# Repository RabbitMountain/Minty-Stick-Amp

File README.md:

# Minty-Stick-Amp
DIY headphone Amplifier for the Chapman Stick

Design in Autodesk Eagle CAD, by me, Andrew Barney, December 2021. **Prototype not yet tested.**

This design is a heavily modified derivitave based on the **"Stick Amp"** by Marcelo Privé, designed and shared sometime between 2002 and 2004. Marcelo Privé's amp was an improved version of Chris Crain's original Chapman **"Stick® Player’s Headphone Amplifier"**, which was built and shared online sometime before 2003. Both designs were centered around the 1969 LM386 Low Voltage Audio Power Amplifier.

The LM386 is one of the most common amps used in DIY guitar preamplifiers due to its ability to run on a single 9V battery. The well-known "Smokey Amp" uses an LM386 and is notable for being able to fit in a cigarette package. The "Ruby" amp is a modified version of a Little Gem amplifier.

In contrast, this prototype design is designed around the more modern LM4819 and TPA321. The design should be compatible with any of the following chips that have the same basic pinout for the SOIC package. Possible IC chips include: LM4819, LM4818?, TPA751, TPA321, TPA741, TPA721, TPA711?, TPA701, TPA301. By using a more modern chip like the LM4819 or the TPA*** family means that it can run on between 2.5 VDC – 5.5 VDC. This means we can run it on a 3.7/4.2V Lipo battery instead of a large 9V battery. Low Power and small size were the main goals of this design, as well as (hopefully) being a functional christmas present for my brother Simmon.

# Schematic

# Sources:

https://web.archive.org/web/20041211021643/http://home.earthlink.net/~cscrain/stick/shpamp.html

https://www.stickist.com/gallery/viewpic.php?pic_id=317

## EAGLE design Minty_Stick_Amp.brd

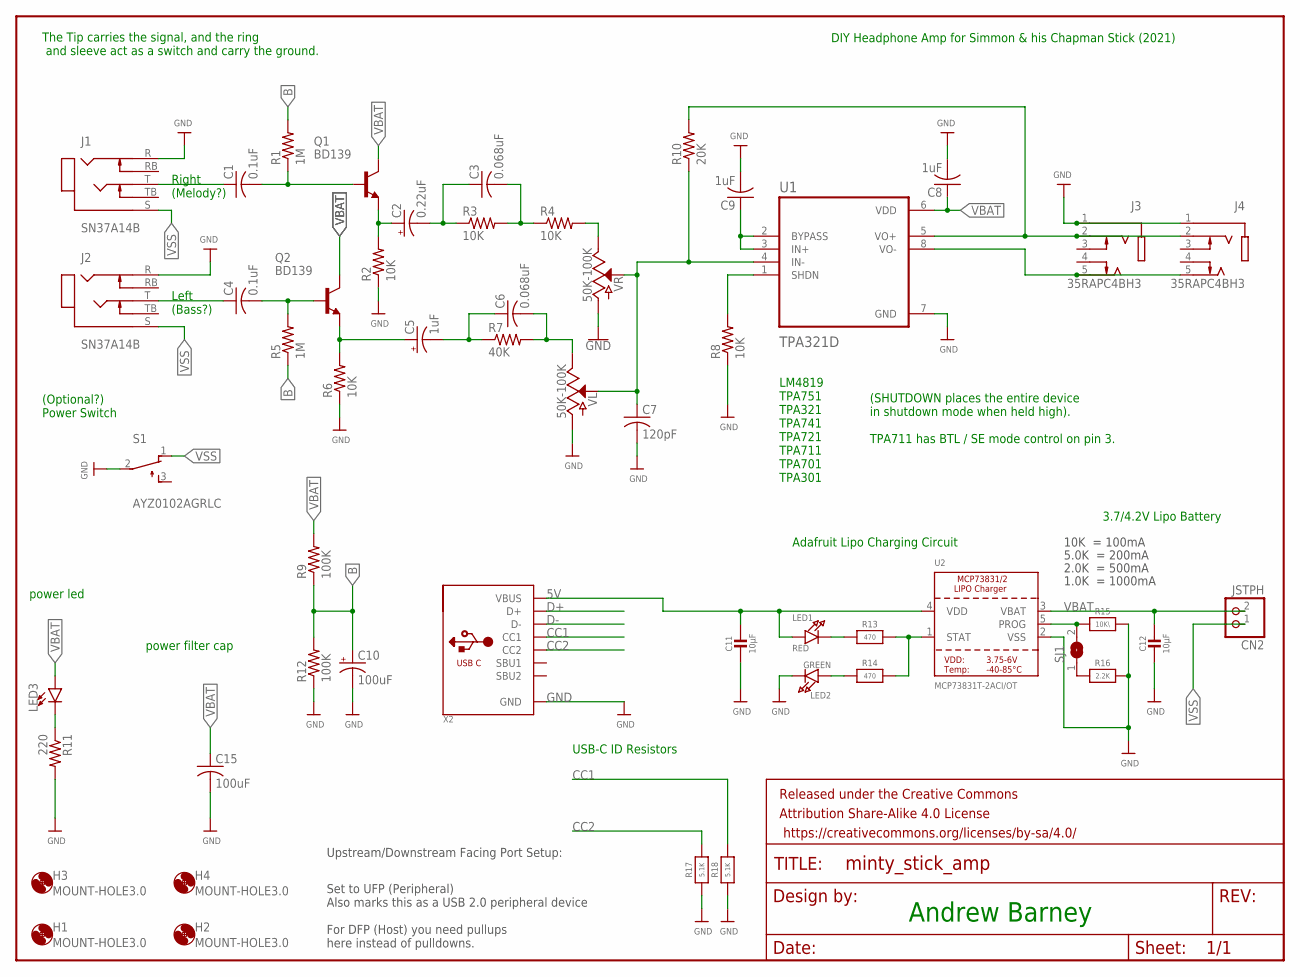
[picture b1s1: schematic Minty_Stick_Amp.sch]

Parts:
C1, C4: 0.1uF; C0805K
C2: 0.22uF; E2,5-6
C3, C6: 0.068uF; C0805K
C5: 1uF; E2,5-6
C7: 120pF; C0805K
C8, C9: 1uF; C0805K
C10: 100uF; E2,5-6
C11, C12: 10µF; _0805
C15: 100uF; C0805K
CN2: JSTPH; JSTPH2
FRAME1: FRAME-LETTERNO_PACKAGE; DUMMY
H1, H2, H3, H4: MOUNT-HOLE3.0; 3,0
J1, J2: SN37A14B; SWITCHCRAFT_SN37A14B
J3, J4: 35RAPC4BH3; SWITCHCRAFT_35RAPC4BH3
LED1: RED; CHIPLED_0805
LED2: GREEN; CHIPLED_0805
LED3: LED3MM; LED_3MM
Q1, Q2: BD139; TO126-V
R1, R5: 1M; M0805
R2, R3, R4, R6, R8: 10K; M0805
R7: 40K; M0805
R9, R12: 100K; M0805
R10: 20K; M0805
R11: 220; 0805-THM-7
R13, R14: 470; _0805
R15: 10K\; _0805
R16: 2.2K; _0805
R17, R18: 5.1K; _0805
S1: AYZ0102AGRLC
SJ1: SOLDERJUMPER; SOLDERJUMPER_ARROW_NOPASTE
U1: TPA321D; SOIC127P599X175-8N
U2: MCP73831T-2ACI/OT; SOT23-5
VL: 50K-100K; POT-PTH-ALPS-KIT
VR: 50K-100K; POT-PTH-ALPS-KIT
X2: USB_C; USB_C_CUSB31-CFM2AX-01-X

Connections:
5V: C11.1, LED1.A, U2.4 (VDD), X2.A4B9 (VBUS), X2.B4A9 (VBUS)
B: C10.+, R1.2, R5.1, R9.1, R12.2
CC1: R18.2, X2.A5 (CC1)
CC2: R17.2, X2.B5 (CC2)
D+: X2.A6 (D+), X2.B6 (D+)
D-: X2.A7 (D-), X2.B7 (D-)
GND: C7.2, C8.2, C9.2, C10.-, C11.2, C12.2, C15.2, J1.R, J2.R, J3.1, J4.1, LED2.C, R2.1, R6.1, R8.1, R11.2, R12.1, R15.2, R16.2, R17.1, R18.1, S1.2, U1.7 (GND), U2.2 (VSS), VL.P$3 (A), VR.P$3 (A), X2.A1B12 (GND), X2.B1A12 (GND)
unnamed: C4.1, J2.T
unnamed: R8.2, U1.1 (SHDN)
unnamed: C1.1, J1.T
unnamed: C1.2, Q1.B, R1.1
unnamed: LED3.K (C), R11.1
unnamed: C4.2, Q2.B, R5.2
unnamed: C2.+, Q1.E, R2.2
unnamed: C5.+, Q2.E, R6.2
unnamed: C2.-, C3.1, R3.1
unnamed: LED1.C, R13.1
unnamed: C3.2, R3.2, R4.1
unnamed: C5.-, C6.1, R7.1
unnamed: C6.2, R7.2, VL.P$1 (E)
unnamed: C9.1, U1.2 (BYPASS), U1.3 (IN+)
unnamed: R4.2, VR.P$1 (E)
unnamed: R13.2, R14.2, U2.1 (STAT)
unnamed: R15.1, SJ1.2, U2.5 (PROG)
unnamed: C7.1, R10.1, U1.4 (IN-), VL.P$2 (S), VR.P$2 (S)
unnamed: LED2.A, R14.1
unnamed: R16.1, SJ1.1
unnamed: J3.2, J4.2, R10.2, U1.5 (VO+)
unnamed: J3.5, J4.5, U1.8 (VO-)
VBAT: C8.1, C12.1, C15.1, CN2.2, LED3.A, Q1.C, Q2.C, R9.2, U1.6 (VDD), U2.3 (VBAT)
VSS: CN2.1, J1.S, J2.S, S1.1

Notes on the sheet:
DIY Headphone Amp for Simmon & his Chapman Stick (2021)
Left (Bass?)
Right (Melody?)
power filter cap
power led
(SHUTDOWN places the entire device in shutdown mode when held high). TPA711 has BTL / SE mode control on pin 3.
LM4819 TPA751 TPA321 TPA741 TPA721 TPA711 TPA701 TPA301
3.7/4.2V Lipo Battery
The Tip carries the signal, and the ring and sleeve act as a switch and carry the ground.
10K = 100mA
5.0K = 200mA
2.0K = 500mA
1.0K = 1000mA
Set to UFP (Peripheral) Also marks this as a USB 2.0 peripheral device For DFP (Host) you need pullups here instead of pulldowns.
Upstream/Downstream Facing Port Setup:
USB-C ID Resistors
Adafruit Lipo Charging Circuit
Andrew Barney
(Optional?) Power Switch

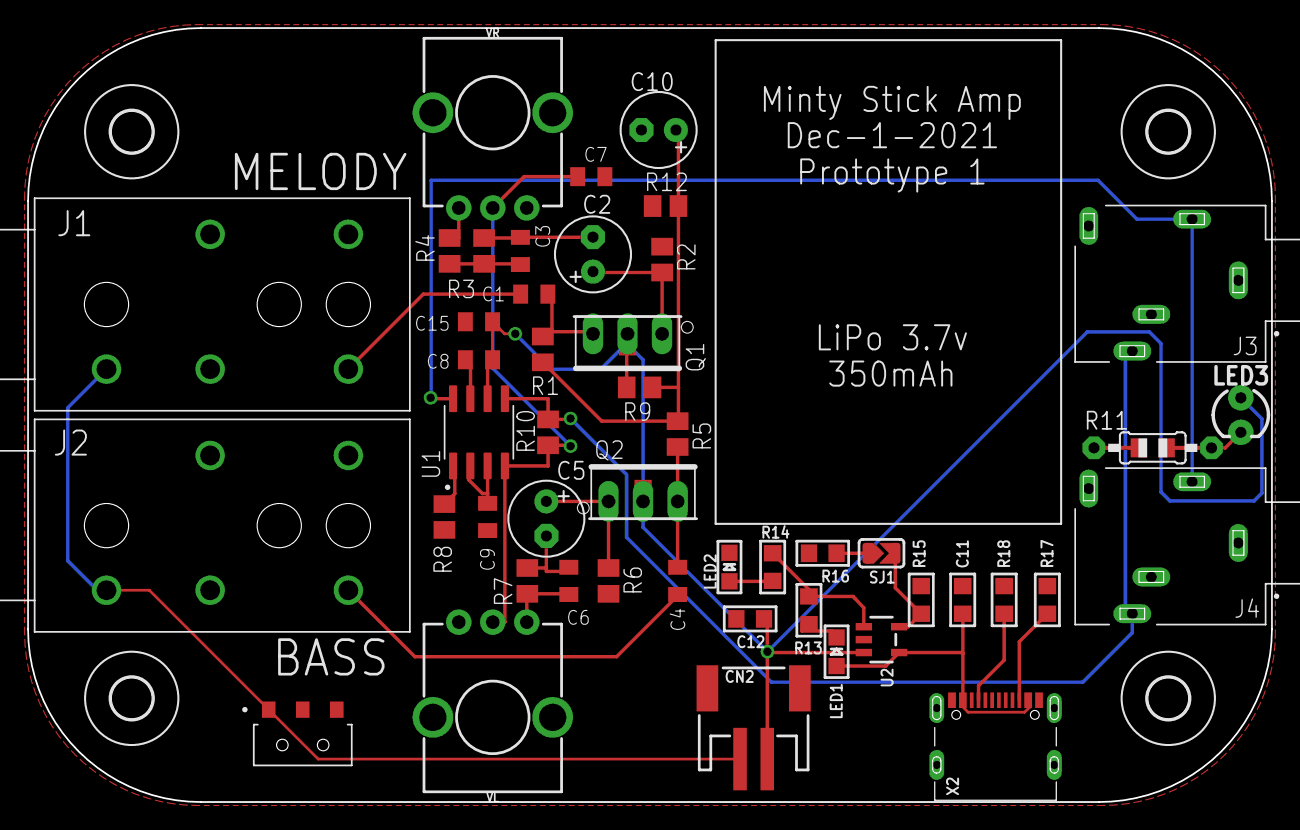
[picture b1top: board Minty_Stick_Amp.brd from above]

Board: 2 copper layers, 91.4 x 56.9 mm, 54 parts (0 on the bottom side), 31 nets.

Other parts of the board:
U$2: ALTOIDSTIN-DIM

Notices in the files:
parts and their libraries:
SparkFun-Aesthetics: Licensing: Creative Commons ShareAlike 4.0 International - https://creativecommons.org/licenses/by-sa/4.0
microbuilder: This work is placed in the public domain, and may be freely used for commercial and non-commercial work with the following conditions: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
